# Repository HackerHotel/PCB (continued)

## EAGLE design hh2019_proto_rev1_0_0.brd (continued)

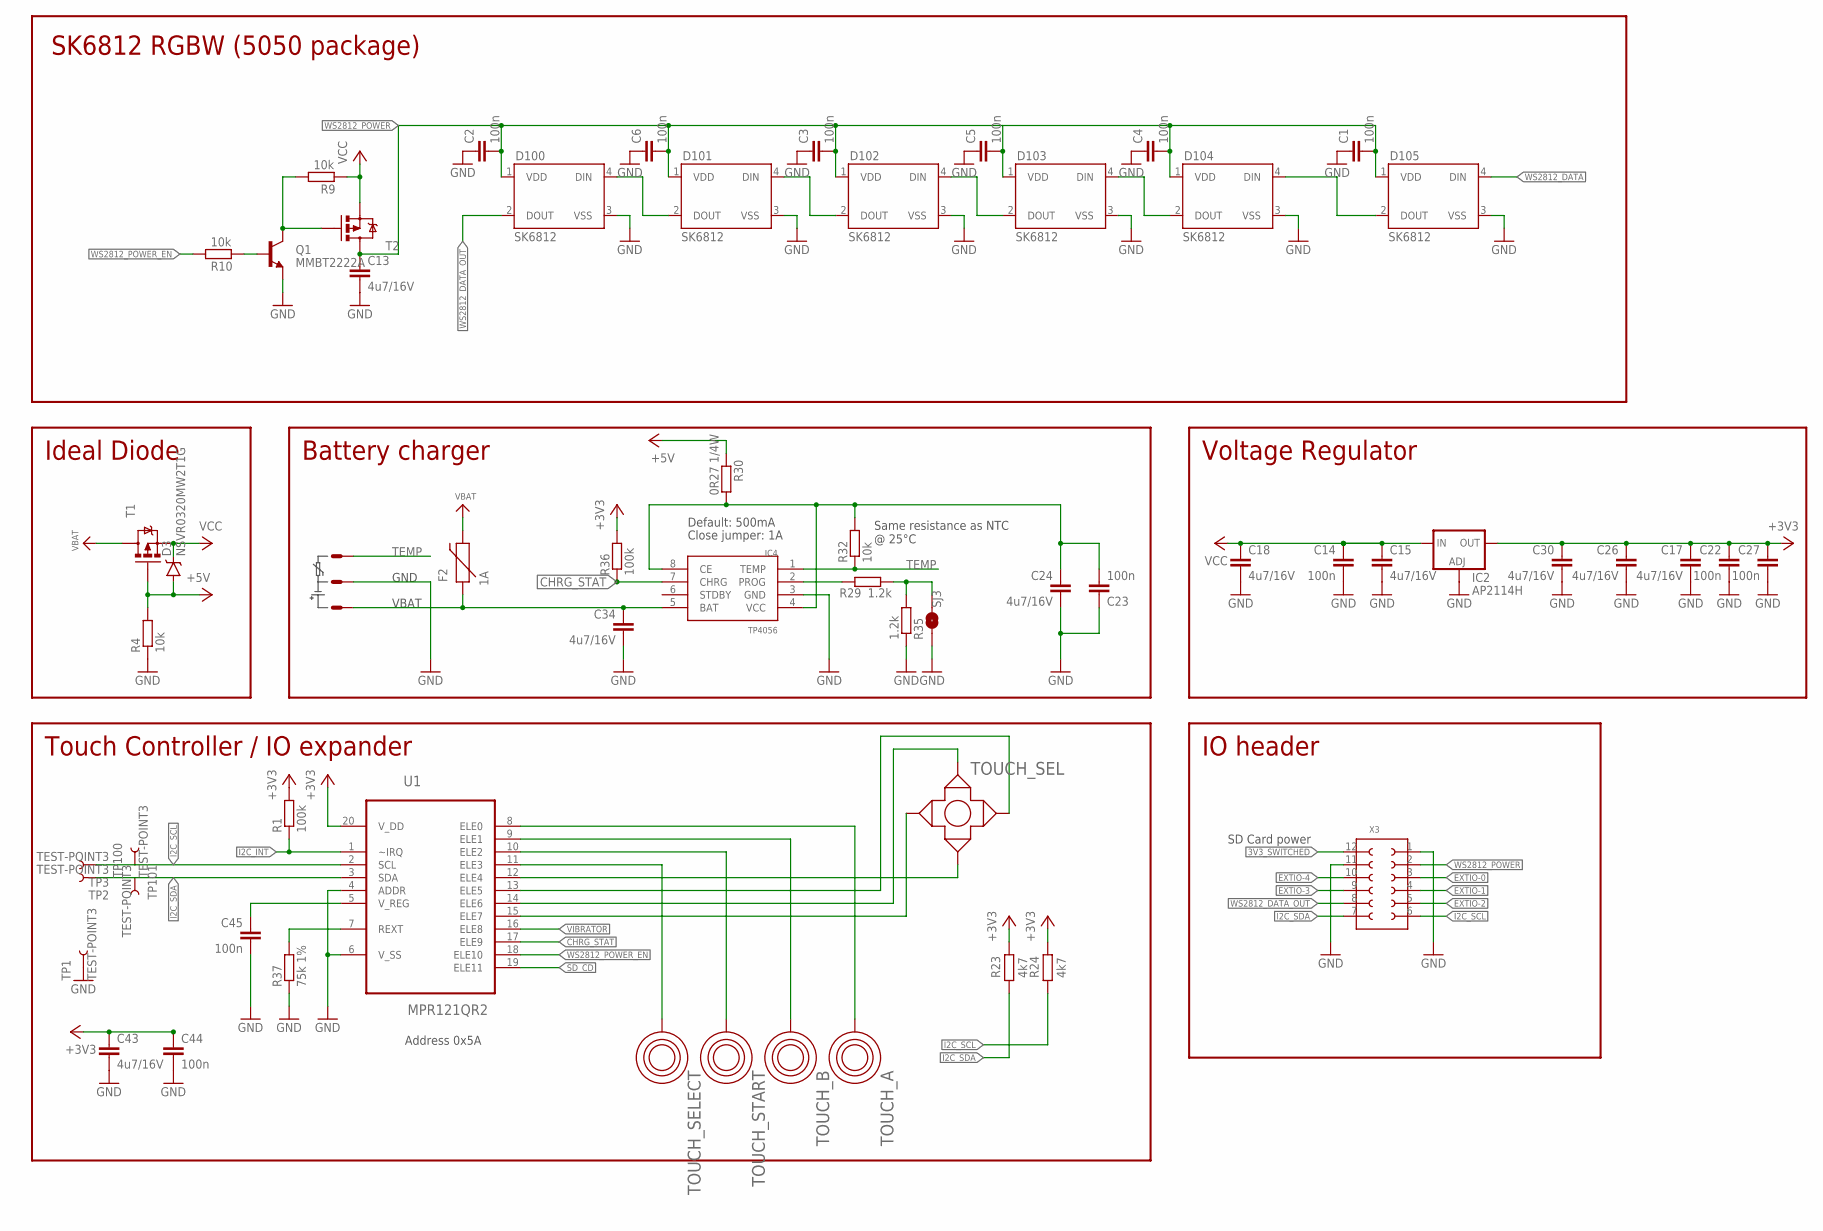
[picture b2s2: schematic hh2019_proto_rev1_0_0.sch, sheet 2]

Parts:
C1, C2, C3, C4, C5, C6, C14, C22, C23, C27, C44, C45: 100n; C0603-DASHES; PARTNO GRM188R71H104KA93D
C13, C15, C17, C18, C24, C26, C30, C34, C43: 4u7/16V; C0805; PARTNO GRM21BR61C475KA88K
D3: NSVR0320MW2T1G; SOD-323; PARTNO BAT20JFILM
D100, D101, D102, D103, D104, D105: SK6812; WS2812B; PARTNO SK6812
F2: 1A; PTC-1206
IC2: AP2114H; SOT223; PARTNO AP7215-33YG-13
IC4: TP4056; SOP-8
Q1: MMBT2222A; SOT23-3; PARTNO BC817-25,215
R1, R36: 100k; R0603-DASHES; PARTNO ERJ-3GEYJ104V
R4, R9, R10: 10k; R0603-DASHES; PARTNO ERJ-3GEYJ103V
R23, R24: 4k7; R0603-DASHES; PARTNO ERJ-3GEYJ103V
R29, R35: 1.2k; R0603-DASHES; PARTNO ERJ-3GEYJ222V
R30: 0R27 1/4W; R1206; PARTNO ERJ-3GEYJ154V
R32: 10k; R0603-DASHES; PARTNO ERJ-3GEYJ154V
R37: 75k 1%; R0603-DASHES; PARTNO ERJ-3GEYJ104V
SJ3: JUMPER-PAD-2-NOYES_SILK; PAD-JUMPER-2-NO_YES_SILK; PARTNO NAP
T1, T2: MOSFET-PCHANNEL; SOT23-3
TOUCH_A: TOUCHROUND; TOUCH_BUTTON; PARTNO NAP
TOUCH_B: TOUCHROUND; TOUCH_BUTTON; PARTNO NAP
TOUCH_SEL: TOUCH_CROSS; PARTNO NAP
TOUCH_SELECT: TOUCHSELECT; TOUCH_SELECT
TOUCH_START: TOUCHSELECT; TOUCH_SELECT
TP1, TP2, TP3, TP100, TP101: TEST-POINT3; PAD.03X.03; PARTNO NAP
U1: MPR121QR2; QFN40P300X300X60-20N
X3: 610X12243021; PARTNO 517-153208-2020-TB
X4: JST-PH3

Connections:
3V3_SWITCHED: X3.12 (1); also elsewhere on the board
+3V3: C17.1, C22.1, C26.1, C27.1, C30.1, C43.1, C44.1, IC2.4 (OUT), R1.2, R23.1, R24.1, R36.2, U1.20 (V_DD); also elsewhere on the board
+5V: D3.A, R4.2, R30.1, T1.1 (G); also elsewhere on the board
CHRG_STAT: IC4.7 (CHRG), R36.1, U1.17 (ELE9)
EXTIO-0: X3.3 (10); also elsewhere on the board
EXTIO-1: X3.4 (9); also elsewhere on the board
EXTIO-2: X3.5 (8); also elsewhere on the board
EXTIO-3: X3.9 (4); also elsewhere on the board
EXTIO-4: X3.10 (3); also elsewhere on the board
GND: C1.1, C2.1, C3.1, C4.1, C5.1, C6.1, C13.2, C14.2, C15.2, C17.2, C18.2, C22.2, C23.1, C24.2, C26.2, C27.2, C30.2, C34.2, C43.2, C44.2, C45.2, D100.3 (VSS), D101.3 (VSS), D102.3 (VSS), D103.3 (VSS), D104.3 (VSS), D105.3 (VSS), IC2.1 (ADJ), IC4.3 (GND), Q1.2 (E), R4.1, R35.2, R37.1, SJ3.1, TP1.P$1, U1.4 (ADDR), U1.6 (V_SS), X3.1 (12), X3.11 (2), X4.2; also elsewhere on the board
I2C_INT: R1.1, U1.1 (~IRQ); also elsewhere on the board
I2C_SCL: R24.2, TP3.P$1, TP100.P$1, U1.2 (SCL), X3.6 (7); also elsewhere on the board
I2C_SDA: R23.2, TP2.P$1, TP101.P$1, U1.3 (SDA), X3.7 (6); also elsewhere on the board
unnamed: TOUCH_B.P$1, U1.9 (ELE1)
unnamed: D100.4 (DIN), D101.2 (DOUT)
unnamed: D103.4 (DIN), D104.2 (DOUT)
unnamed: D104.4 (DIN), D105.2 (DOUT)
unnamed: TOUCH_A.P$1, U1.8 (ELE0)
unnamed: IC4.2 (PROG), R29.1
unnamed: R29.2, R35.1, SJ3.2
unnamed: C23.2, C24.1, IC4.4 (VCC), IC4.8 (CE), R30.2, R32.2
unnamed: D101.4 (DIN), D102.2 (DOUT)
unnamed: C45.1, U1.5 (V_REG)
unnamed: R37.2, U1.7 (REXT)
unnamed: TOUCH_START.P$1, U1.10 (ELE2)
unnamed: TOUCH_SELECT.P$1, U1.11 (ELE3)
unnamed: TOUCH_SEL.D (DOWN), U1.12 (ELE4)
unnamed: TOUCH_SEL.L (LEFT), U1.15 (ELE7)
unnamed: TOUCH_SEL.UP, U1.14 (ELE6)
unnamed: TOUCH_SEL.R (RIGHT), U1.13 (ELE5)
unnamed: C34.1, F2.1, IC4.5 (BAT), X4.3
unnamed: D102.4 (DIN), D103.2 (DOUT)
unnamed: Q1.1 (B), R10.2
unnamed: Q1.3 (C), R9.1, T2.1 (G)
SD_CD: U1.19 (ELE11); also elsewhere on the board
TEMP: IC4.1 (TEMP), R32.1, X4.1
VBAT: F2.2, T1.3 (D); also elsewhere on the board
VCC: C14.1, C15.1, C18.1, D3.C, IC2.3 (IN), R9.2, T1.2 (S), T2.2 (S); also elsewhere on the board
VIBRATOR: U1.16 (ELE8); also elsewhere on the board
WS2812_DATA: D105.4 (DIN); also elsewhere on the board
WS2812_DATA_OUT: D100.2 (DOUT), X3.8 (5)
WS2812_POWER: C1.2, C2.2, C3.2, C4.2, C5.2, C6.2, C13.1, D100.1 (VDD), D101.1 (VDD), D102.1 (VDD), D103.1 (VDD), D104.1 (VDD), D105.1 (VDD), T2.3 (D), X3.2 (11); also elsewhere on the board
WS2812_POWER_EN: R10.1, U1.18 (ELE10); also elsewhere on the board

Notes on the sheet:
Voltage Regulator
Battery charger
Ideal Diode
Default: 500mA
Close jumper: 1A
GND
VBAT
Same resistance as NTC @ 25°C
SK6812 RGBW (5050 package)
Touch Controller / IO expander
Address 0x5A
IO header
SD Card power

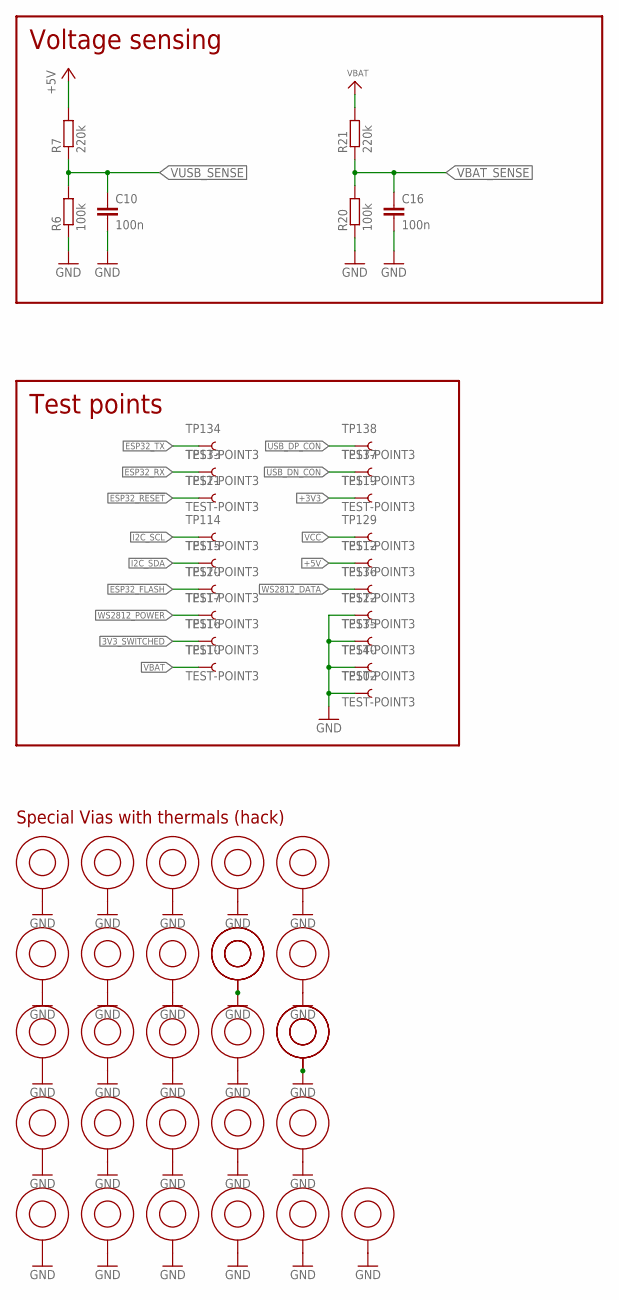
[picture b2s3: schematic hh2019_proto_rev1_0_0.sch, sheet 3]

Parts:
$$U$1, $$U$2, $$U$3, $$U$4, $$U$5, $$U$6, $$U$7, $$U$8, $$U$9: VIA; PARTNO NAP
C10, C16: 100n; C0603-DASHES; PARTNO GRM188R71H104KA93D
R6, R20: 100k; R0603-DASHES; PARTNO ERJ-3GEYJ104V
R7, R21: 220k; R0603-DASHES; PARTNO ERJ-3GEYJ224V
TP102, TP110, TP112, TP114, TP115, TP116, TP117, TP119, TP120, TP121, TP122, TP129, TP133, TP134, TP135, TP136, TP137, TP138, TP140: TEST-POINT3; PAD.03X.03; PARTNO NAP
U$2, U$3, U$4, U$5, U$6, U$10, U$11, U$12, U$13, U$14, U$15, U$16, U$17, U$18, U$19, U$20, U$21, U$22, U$23: VIA; PARTNO NAP

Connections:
3V3_SWITCHED: TP116.P$1; also elsewhere on the board
+3V3: TP119.P$1; also elsewhere on the board
+5V: R7.2, TP112.P$1; also elsewhere on the board
ESP32_!RESET: TP121.P$1; also elsewhere on the board
ESP32_FLASH: TP120.P$1; also elsewhere on the board
ESP32_RX: TP133.P$1; also elsewhere on the board
ESP32_TX: TP134.P$1; also elsewhere on the board
GND: $$U$1.P$1, $$U$2.P$1, $$U$3.P$1, $$U$4.P$1, $$U$5.P$1, $$U$6.P$1, $$U$7.P$1, $$U$8.P$1, $$U$9.P$1, C10.2, C16.2, R6.1, R20.1, TP102.P$1, TP122.P$1, TP135.P$1, TP140.P$1, U$2.P$1, U$3.P$1, U$4.P$1, U$5.P$1, U$6.P$1, U$10.P$1, U$11.P$1, U$12.P$1, U$13.P$1, U$14.P$1, U$15.P$1, U$16.P$1, U$17.P$1, U$18.P$1, U$19.P$1, U$20.P$1, U$21.P$1, U$22.P$1, U$23.P$1; also elsewhere on the board
I2C_SCL: TP114.P$1; also elsewhere on the board
I2C_SDA: TP115.P$1; also elsewhere on the board
USB_DN_CON: TP137.P$1; also elsewhere on the board
USB_DP_CON: TP138.P$1; also elsewhere on the board
VBAT: R21.2, TP110.P$1; also elsewhere on the board
VBAT_SENSE: C16.1, R20.2, R21.1; also elsewhere on the board
VCC: TP129.P$1; also elsewhere on the board
VUSB_SENSE: C10.1, R6.2, R7.1; also elsewhere on the board
WS2812_DATA: TP136.P$1; also elsewhere on the board
WS2812_POWER: TP117.P$1; also elsewhere on the board

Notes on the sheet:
Special Vias with thermals (hack)
Test points
Voltage sensing

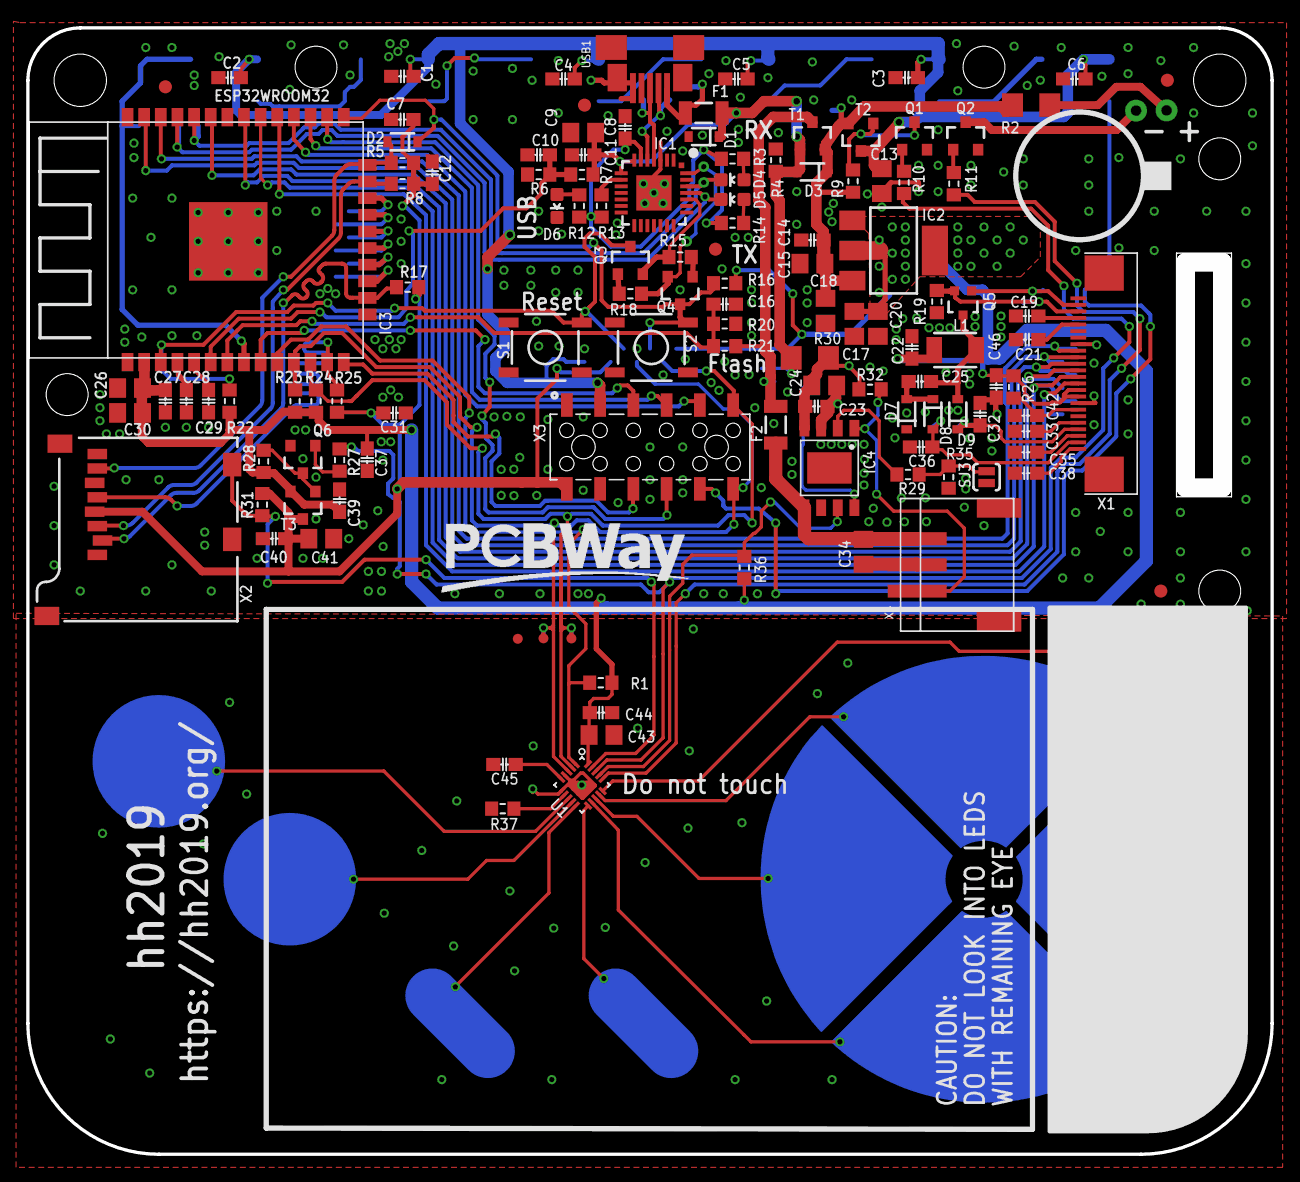
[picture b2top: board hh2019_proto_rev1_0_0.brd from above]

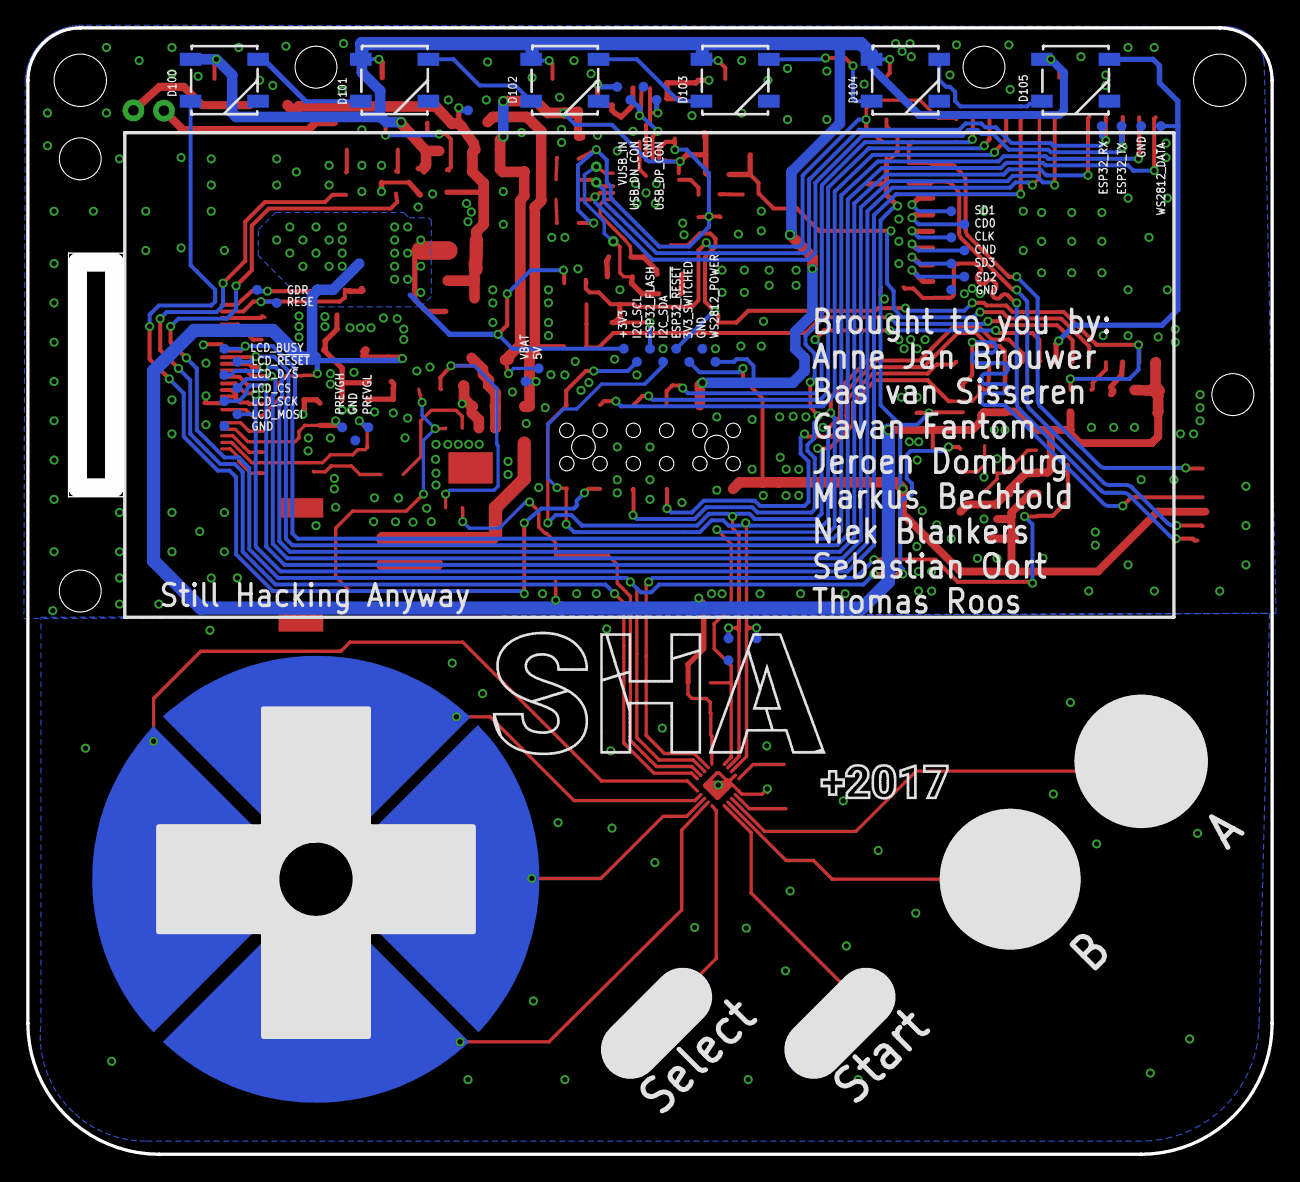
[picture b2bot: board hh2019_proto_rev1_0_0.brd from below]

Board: 2 copper layers, 95.0 x 86.0 mm, 204 parts (52 on the bottom side), 96 nets.

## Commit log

2018-11-04 Initialised fork from SHA2017 for HackerHotel 2019
2018-11-12 Added DAC + 3.5mm socket, working on board
2018-11-12 Fixed severed F/B annotation
2018-11-12 Fixed net names on DAC
2018-11-13 Fixed ESP32 net labels, removed SD card components, working on layout
2018-11-13 Cleaned up old schematic and board
2018-11-13 Removed some bypass caps from DAC
2018-11-13 Prepping layout
2018-11-13 Added net names for touch controller pins (will remap touch buttons for easy routing later)
2018-11-14 Collected components in groups in board design
2018-11-14 Reassigned touch controller pins for easier layouting, got proper main component placement on board
2018-11-14 Placed major components, working on passives
2018-11-15 Routing tracks
2018-11-15 Added most non-bypass passives
2018-11-15 All but the last handful passives placed and routed
2018-11-15 All components placed
2018-11-15 Fixed DRC errors
2018-11-16 Shrunk PCB dimensions, added version and credits
2018-12-20 Added missing DAC connections. Fixes #1
2018-12-20 Fixed floating DAC pins being unconnected
2018-12-20 Increased touch trace robustness, and added proper passthrough of back groundplane
2018-12-20 Made board smaller, placed caps closer to touch controller, increased free space around display connector, implemented dull brick PCB design. Fixes issues #2 #3 #4.
2018-12-28 Finished PCB design. Added Shitty AddOn, IR, buzzer
2018-12-29 Added moar cybar
2018-12-29 Added Renze's superfluous Grove connector
2018-12-31 Finished design, exported BOM and centroid files, and created gerbers
2020-10-05 Document that you can open this in KiCad
